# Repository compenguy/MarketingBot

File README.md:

# Mark

See the attached Wiki for documentation about the general system functionality

## Supported Libraries 

See [Libraries](./libraries/README.md) for how to install the necessary libraries to compile and modify code.

## Hardware Support
Information regarding the custom boards used on this project use [Kicad](https://www.kicad.org/).

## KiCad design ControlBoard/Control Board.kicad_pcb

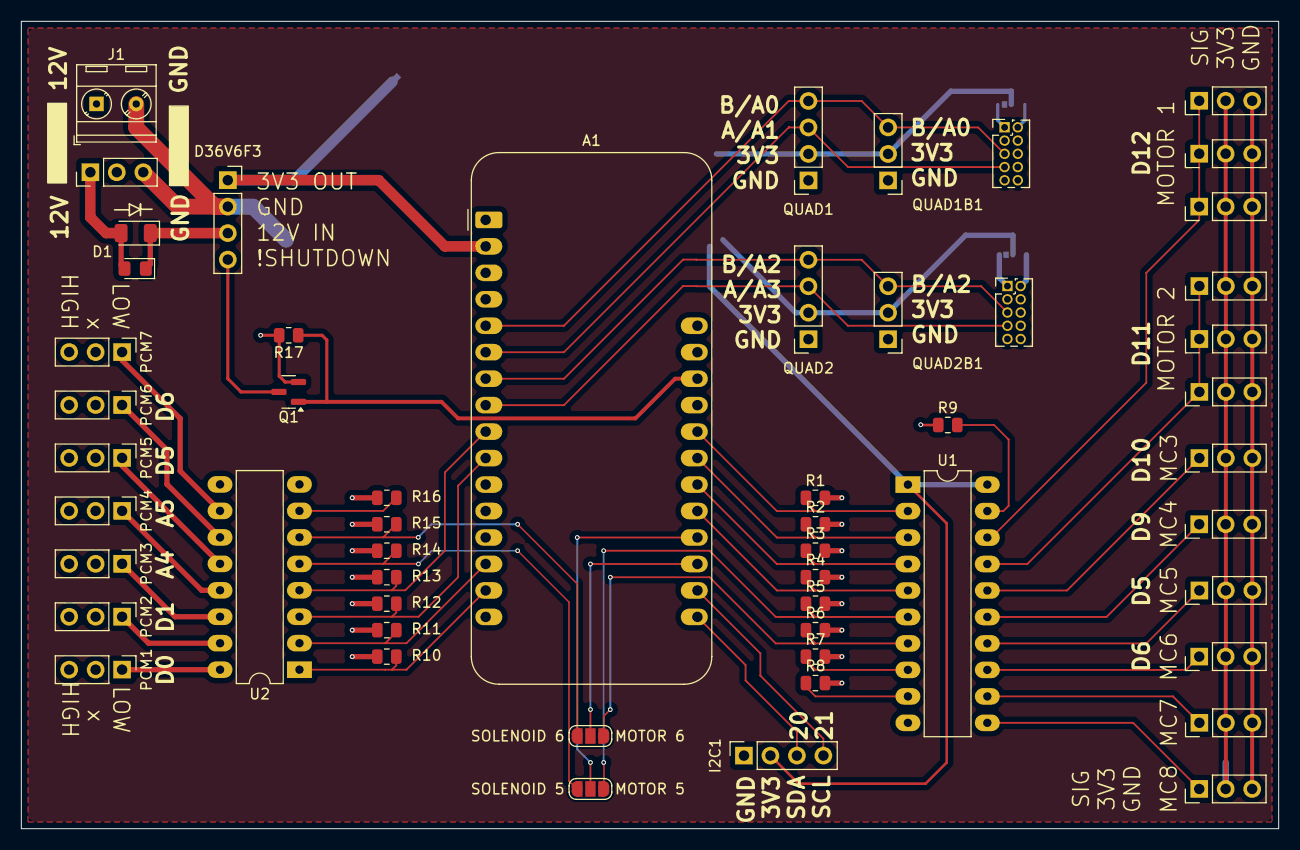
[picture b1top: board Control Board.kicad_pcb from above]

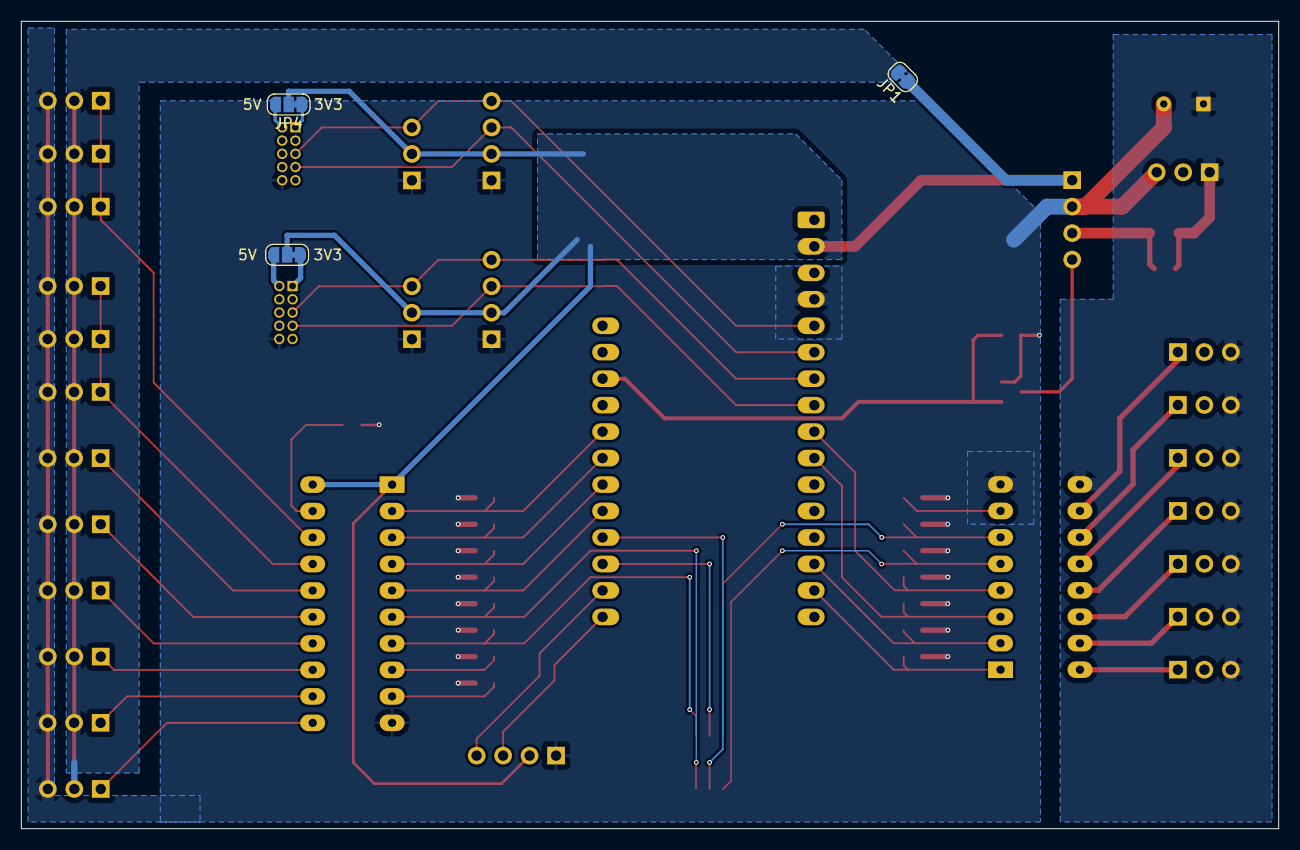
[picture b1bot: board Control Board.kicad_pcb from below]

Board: 2 copper layers, 120.7 x 77.5 mm, 57 parts (3 on the bottom side), 50 nets.

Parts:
12V_INPUT1: Conn_01x03_Pin; PinHeader_1x03_P2.54mm_Vertical
A1: Adafruit_Feather_M0_RFM9x_LoRa_Radio; Adafruit_Feather_M0_RFM
D1: D; D_1206_3216Metric
D2: D; D_0805_2012Metric_Pad1.15x1.40mm_HandSolder
D36V6F3: Conn_01x04_Pin; PinSocket_1x04_P2.54mm_Vertical
I2C1: Conn_01x04_Pin; PinSocket_1x04_P2.54mm_Vertical
J1: Conn_01x02_Pin; TerminalBlock_MetzConnect_Type086_RT03402HBLC_1x02_P3.81mm_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
JP1: SolderJumper_2_Bridged; SolderJumper-2_P1.3mm_Bridged_RoundedPad1.0x1.5mm
JP2, JP3: SolderJumper_3_Open; SolderJumper-3_P1.3mm_Open_RoundedPad1.0x1.5mm_NumberLabels
JP4, JP5: SolderJumper_3_Open; SolderJumper-3_P1.3mm_Bridged12_RoundedPad1.0x1.5mm_NumberL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
MC1A1, MC1B1, MC1C1, MC2A1, MC2B1, MC2C1, MC3, MC4, MC5, MC6, MC7, MC8: Conn_01x03_Pin; PinHeader_1x03_P2.54mm_Vertical
PCM1, PCM2, PCM3, PCM4, PCM5, PCM6, PCM7: Conn_01x03_Pin; PinHeader_1x03_P2.54mm_Vertical
Q1: BSS138; SOT-23
QUAD1, QUAD2: Conn_01x04_Pin; PinSocket_1x04_P2.54mm_Vertical
QUAD1B1, QUAD2B1: Conn_01x03_Pin; PinHeader_1x03_P2.54mm_Vertical
QUAD1_CTRE1, QUAD2_CTRE1: 3220-10-0100-00; PinHeader_2x05_P1.27mm_Vertical
R1, R2, R3, R4, R5, R6, R7, R8: 10k; R_0805_2012Metric
R9, R10, R11, R12, R13, R14, R15, R16, R17: 10kOhms; R_0805_2012Metric
U1: SN74LVC245APW; DIP-20_W7.62mm_LongPads
U2: ULN2003; DIP-16_W7.62mm_LongPads

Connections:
+3V3: A1.2 (3V3), D36V6F3.1, I2C1.2, JP1.1 (A), JP4.2 (C), JP5.2 (C), QUAD1.2, QUAD1B1.2, QUAD2.2, QUAD2B1.2, U1.1 (DIR), U1.20 (VCC)
+5V: JP1.2 (B), MC1A1.2, MC1B1.2, MC1C1.2, MC2A1.2, MC2B1.2, MC2C1.2, MC3.2, MC4.2, MC5.2, MC6.2, MC7.2, MC8.2
+12V: 12V_INPUT1.1, D1.2 (A), D2.2 (A), J1.1, PCM1.3, PCM2.3, PCM3.3, PCM4.3, PCM5.3, PCM6.3, PCM7.3, U2.9 (COM)
/!SHUTDOWN: D36V6F3.4, Q1.3 (D)
/+12VDC_REG: D1.1 (K), D2.1 (K), D36V6F3.3
/MOTOR #1 OUTPUT: MC1A1.1, MC1B1.1, MC1C1.1, U1.18 (B1)
/MOTOR #2 OUTPUT: MC2A1.1, MC2B1.1, MC2C1.1, U1.17 (B2)
/MOTOR #3 OUTPUT: MC3.1, U1.16 (B3)
/MOTOR #4 OUTPUT: MC4.1, U1.15 (B4)
/MOTOR #5 OUTPUT: MC5.1, U1.14 (B5)
/MOTOR #6 OUTPUT: MC6.1, U1.13 (B6)
/MOTOR #7 OUTPUT: MC7.1, U1.12 (B7)
/MOTOR #8 OUTPUT: MC8.1, U1.11 (B8)
/Q1_3V3: JP4.1 (A), QUAD1_CTRE1.1
/Q2_3V3: JP5.1 (A), QUAD2_CTRE1.1
/SOL1: PCM1.1, U2.16 (O1)
/SOL2: PCM2.1, U2.15 (O2)
/SOL3: PCM3.1, U2.14 (O3)
/SOL4: PCM4.1, U2.13 (O4)
/SOL5: PCM5.1, U2.12 (O5)
/SOL6: PCM6.1, U2.11 (O6)
/SOL7: PCM7.1, U2.10 (O7)
GND: 12V_INPUT1.3, A1.4 (GND), D36V6F3.2, I2C1.1, J1.2, MC1A1.3, MC1B1.3, MC1C1.3, MC2A1.3, MC2B1.3, MC2C1.3, MC3.3, MC4.3, MC5.3, MC6.3, MC7.3, MC8.3, Q1.2 (S), QUAD1.1, QUAD1B1.1, QUAD1_CTRE1.10, QUAD2.1, QUAD2B1.1, QUAD2_CTRE1.10, R1.2, R2.2, R3.2, R4.2, R5.2, R6.2, R7.2, R8.2, R9.1, R10.2, R11.2, R12.2, R13.2, R14.2, R15.2, R16.2, R17.2, U1.10 (GND), U2.8 (GND)
IO5: A1.20 (D6), JP3.2 (C)
IO6: A1.19 (D5), JP2.2 (C)
MC1: A1.24 (D12), R1.1, U1.2 (A1)
MC2: A1.23 (D11), R2.1, U1.3 (A2)
MC3: A1.22 (D10), R3.1, U1.4 (A3)
MC4: A1.21 (D9), R4.1, U1.5 (A4)
MC5: JP3.1 (A), R5.1, U1.6 (A5)
MC6: JP2.1 (A), R6.1, U1.7 (A6)
MC7: R7.1, U1.8 (A7)
MC8: R8.1, U1.9 (A8)
unnamed: A1.18 (SCL/D21), I2C1.4
unnamed: A1.17 (SDA/D20), I2C1.3
unnamed: JP4.3 (B), QUAD1_CTRE1.2
unnamed: JP5.3 (B), QUAD2_CTRE1.2
unnamed: R9.2, U1.19 (~OE)
PC1: A1.15 (TX/D1), R10.1, U2.1 (I1)
PC2: A1.14 (RX/D0), R11.1, U2.2 (I2)
PC3: A1.10 (A5), R12.1, U2.3 (I3)
PC4: A1.9 (A4), R13.1, U2.4 (I4)
PC5: JP3.3 (B), R14.1, U2.5 (I5)
PC6: JP2.3 (B), R15.1, U2.6 (I6)
PC7: R16.1, U2.7 (I7)
QUAD_1A: A1.6 (A1), QUAD1.3, QUAD1_CTRE1.7
QUAD_1B: A1.5 (DAC0/A0), QUAD1.4, QUAD1B1.3, QUAD1_CTRE1.5
QUAD_2A: A1.8 (A3), QUAD2.3, QUAD2_CTRE1.7
QUAD_2B: A1.7 (A2), QUAD2.4, QUAD2B1.3, QUAD2_CTRE1.5
VUSB: A1.26 (USB), Q1.1 (G), R17.1

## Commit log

2025-07-23 Fixes +Y axis saturating too quickly
    Y axis was returning +1000 through ~half the downward travel of the
    stick. This change gives a smooth ramp from center to bottom going from
    0 to +1000.
2025-07-23 Removing the SleepyDog library include - it's not used
2025-07-23 Update libraries readme for a duplicate library and a missing library
2025-07-26 Minor documentation updates
2025-10-16 Refactor Marketing bot lib and Tshirt cannon
2025-10-16 Update to Control Board
